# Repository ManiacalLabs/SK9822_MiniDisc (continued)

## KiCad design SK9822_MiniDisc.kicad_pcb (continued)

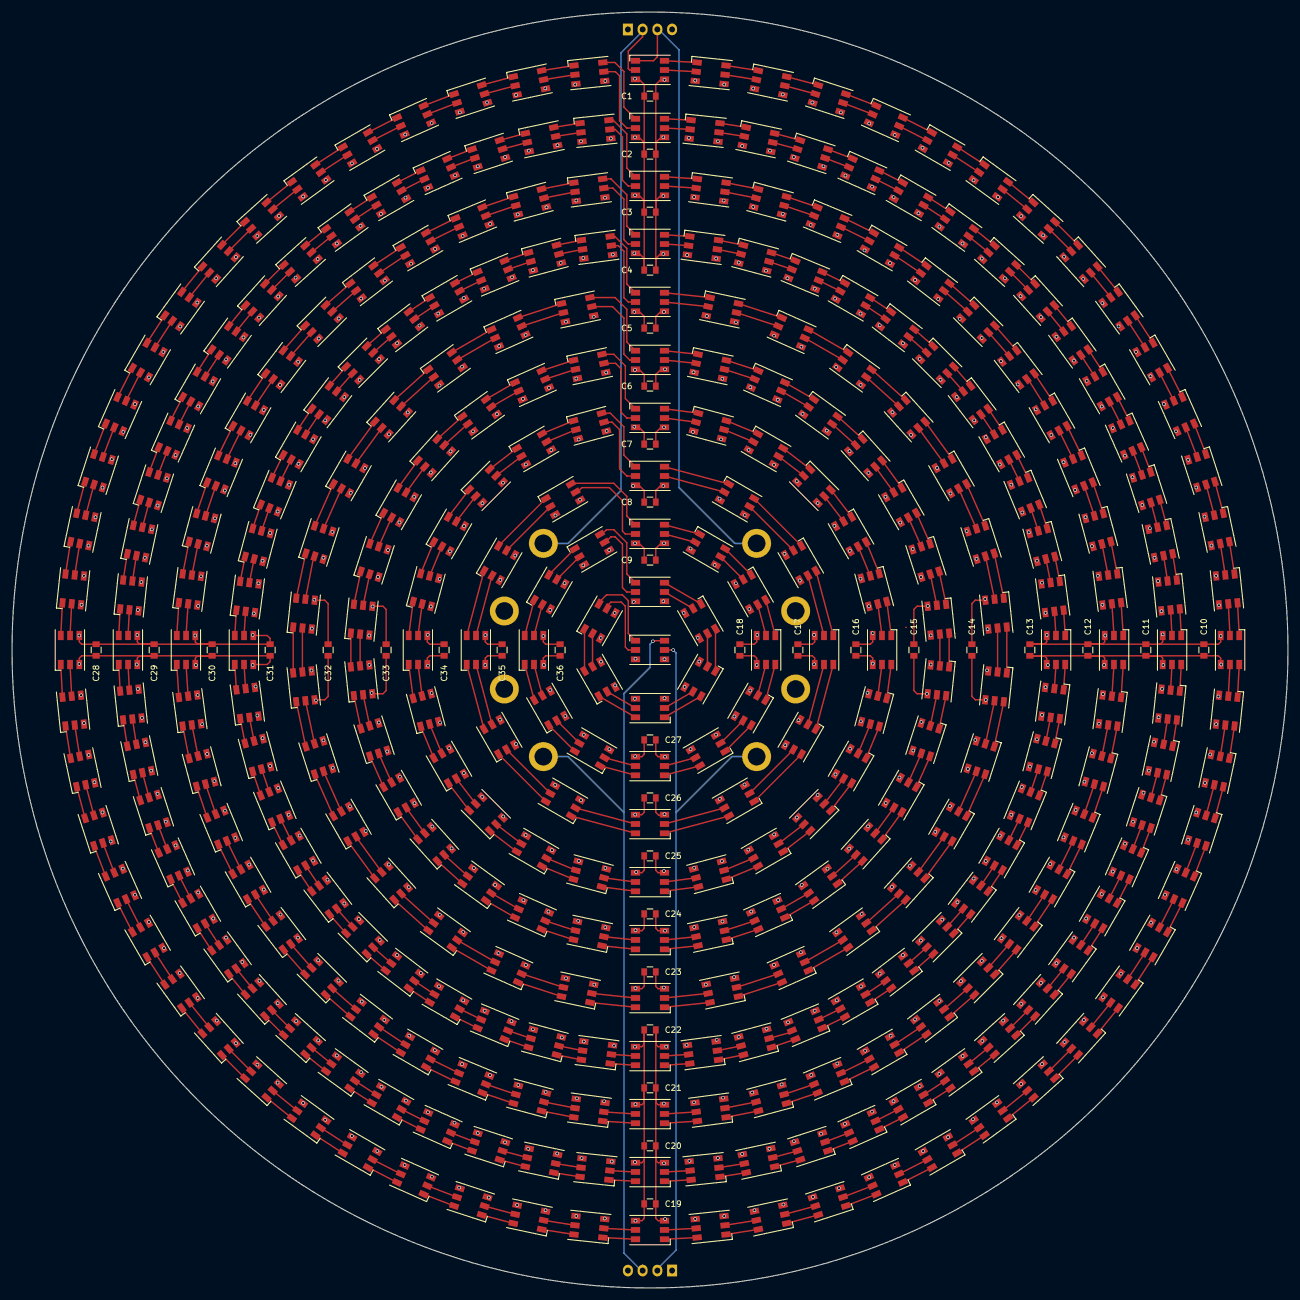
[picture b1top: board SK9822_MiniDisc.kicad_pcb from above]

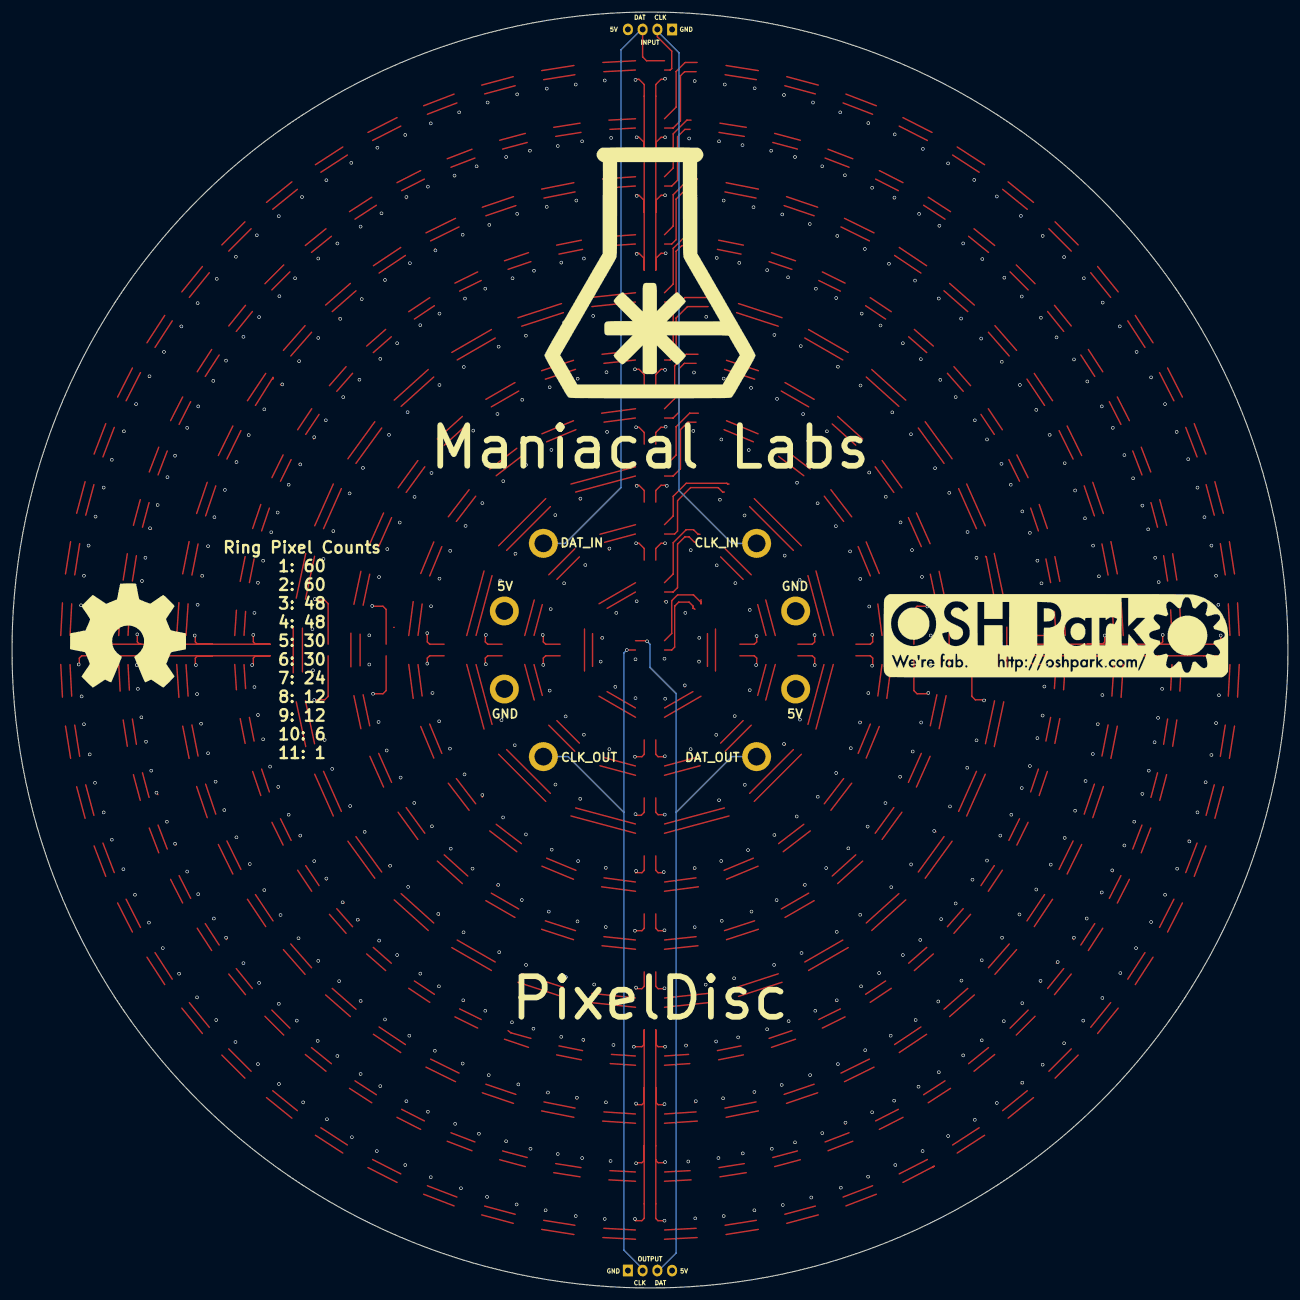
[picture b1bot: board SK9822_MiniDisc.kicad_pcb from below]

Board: 4 copper layers, 220.0 x 220.0 mm, 369 parts (2 on the bottom side), 666 nets.

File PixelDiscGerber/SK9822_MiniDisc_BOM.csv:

"Id";"Designator";"Package";"Quantity";"Designation";"Supplier and ref";
1;"C18,C27,C36,C17,C26,C35,C16,C25,C34,C15,C24,C33,C14,C23,C32,C13,C22,C31,C12,C21,C30,C11,C20,C29,C10,C19,C28,C9,C8,C7,C6,C5,C4,C3,C2,C1";"C_0805";36;"10uF";;;
2;"D321,D323,D326,D327,D328,D329,D330,D314,D315,D316,D317,D318,D319,D320,D322,D324,D302,D303,D304,D305,D306,D307,D308,D309,D310,D311,D312,D278,D279,D280,D281,D282,D283,D284,D285,D286,D287,D288,D289,D290,D291,D292,D293,D294,D295,D296,D297,D298,D299,D300,D331,D325,D313,D301,D277,D248,D249,D250,D251,D252,D253,D254,D255,D256,D257,D258,D259,D260,D261,D262,D263,D264,D265,D266,D267,D268,D269,D270,D271,D272,D273,D274,D275,D276,D218,D219,D220,D221,D222,D223,D224,D225,D226,D227,D228,D229,D230,D231,D232,D233,D234,D235,D236,D237,D238,D239,D240,D241,D242,D243,D244,D245,D246,D170,D171,D172,D173,D174,D175,D176,D177,D178,D179,D180,D181,D182,D183,D184,D185,D186,D187,D188,D189,D190,D191,D192,D193,D194,D195,D196,D197,D198,D199,D200,D201,D202,D203,D204,D205,D206,D207,D208,D209,D210,D211,D212,D213,D214,D215,D216,D122,D123,D124,D125,D126,D127,D128,D129,D130,D131,D132,D133,D134,D135,D136,D137,D138,D139,D140,D141,D142,D143,D144,D145,D146,D147,D148,D149,D150,D151,D152,D153,D154,D155,D156,D157,D158,D159,D160,D161,D162,D163,D164,D165,D166,D167,D168,D247,D217,D169,D121,D62,D63,D64,D65,D66,D67,D68,D69,D70,D71,D72,D73,D74,D75,D76,D77,D78,D79,D80,D81,D82,D83,D84,D85,D86,D87,D88,D89,D90,D91,D92,D93,D94,D95,D96,D97,D98,D99,D100,D101,D102,D103,D104,D105,D106,D107,D108,D109,D110,D111,D112,D113,D114,D115,D116,D117,D118,D119,D120,D61,D2,D3,D4,D5,D6,D7,D8,D9,D10,D11,D12,D13,D14,D15,D16,D17,D18,D19,D20,D21,D22,D23,D24,D25,D26,D27,D28,D29,D30,D31,D32,D33,D34,D35,D36,D37,D38,D39,D40,D41,D42,D43,D44,D45,D46,D47,D48,D49,D50,D51,D52,D53,D54,D55,D56,D57,D58,D59,D60,D1";"SK9822";331;"APA102/SK9822";;;

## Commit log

2017-06-16 fixing footprint refs
2017-06-16 Complete signal routing. Power needed
2017-06-16 tweaks to signal routing
2017-06-16 further signal line tweaks
2017-06-24 4 layer
2017-06-24 Grounds laid
2017-06-24 starting gnd plane
2017-06-24 more gnd plane
2017-06-25 full gnd layout
2017-06-25 adding caps
2017-06-25 places caps
2017-06-25 finaly got caps right
2017-06-25 everything routed
2017-06-25 removed extraneous caps
2017-06-25 added copper pours
2017-06-25 added lables
2017-06-25 Full layout and labels
2017-06-25 Adding gerbers
2017-07-04 fixing unconnected
2017-07-04 Added vias to D99 and D156 VCC
2017-07-04 Fixed unconnected again
2017-07-04 adding more logos
2017-07-05 Updated Gerbers and fab outputs
